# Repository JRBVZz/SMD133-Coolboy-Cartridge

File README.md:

#### COOLBOY - картридж многоигровка для Денди/Famicom

Картридж основан на ASIC **AA6023** в корпусе LQFP-48 с маркировкой **SMD133** и имеет следующие характеристики:
* **PRG ROM**: до 32 МБ
* **CHR RAM**: до 256 КБ
* **PRG RAM**: 8/32 КБ, FRAM или SRAM

Проект создан в [**KiCad 9**](https://www.kicad.org/).

#### Параметры для изготовления PCB
* 2 слоя
* Толщина PCB: 1.2 мм
* Рекомендуется ENIG покрытие контактов краевого разъема

#### Схема
[Schematic PDF](Pics/Coolboy-schematic.pdf)

#### Интерактивный BOM
[BoM](BOM/Coolboy-iBOM.html) (для корректного просмотра нужно скачать raw файл)

#### Прошивка
Для прошивки картриджа без пайки, перемычка должна соединять среднюю и нижнюю площадки у джампера "R/W". Картридж можно перепрошить с помощью [Famicom/NES Dumper/Writer](https://github.com/ClusterM/famicom-dumper-writer), собрать ROM-файл можно в [COOLBOY Multirom Builder](https://github.com/ClusterM/coolboy-multirom-builder). Спасибо Алексею Кластеру за эти отличные инструменты.

PS Герберы не выкладываю специально - это мой небольшой вклад в популяризацию KiCad :smile:

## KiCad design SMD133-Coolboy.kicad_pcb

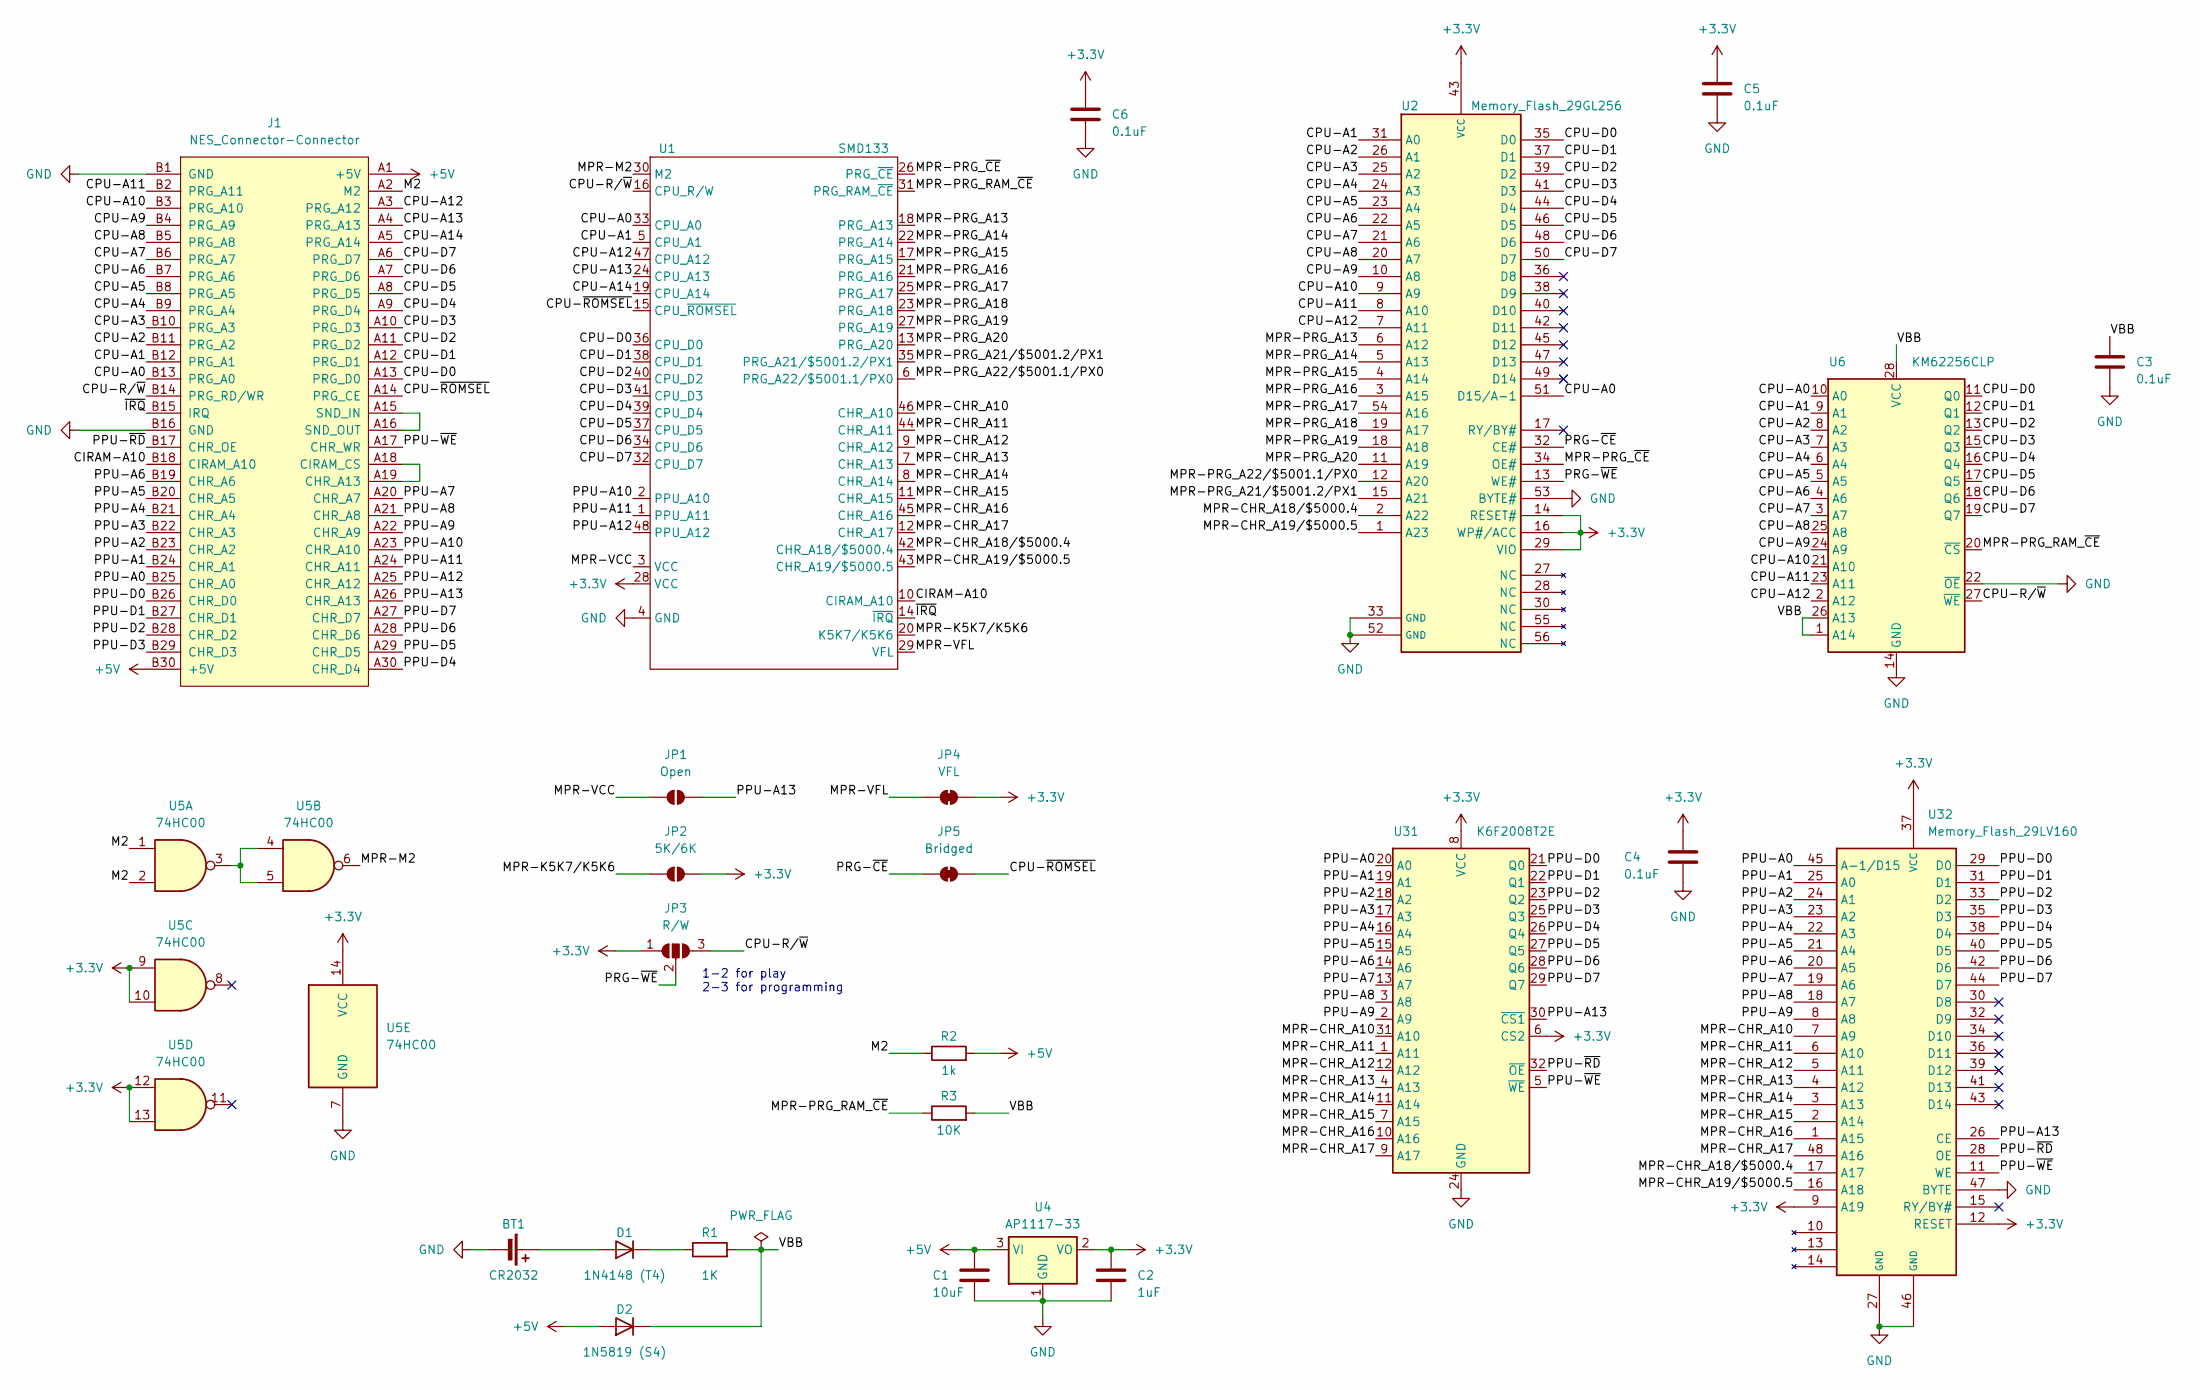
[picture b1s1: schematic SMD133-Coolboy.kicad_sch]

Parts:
BT1: CR2032; BatteryHolder_2032
C1: 10uF; C_0805_2012Metric
C2: 1uF; C_0805_2012Metric
C3, C4, C5, C6: 0.1uF; C_0603_1608Metric_Pad1.08x0.95mm_HandSolder
D1: 1N4148 (T4); D_SOD-123
D2: 1N5819 (S4); D_SOD-123
J1: NES_Connector-Connector; NES_Connector_L
JP1: Open; SolderJumper-2_P1.3mm_Open_RoundedPad1.0x1.5mm
JP2: 5K/6K; SolderJumper-2_P1.3mm_Open_RoundedPad1.0x1.5mm
JP3: R/W; SolderJumper-3_P1.3mm_Open_RoundedPad1.0x1.5mm
JP4: VFL; SolderJumper-2_P1.3mm_Bridged_RoundedPad1.0x1.5mm
JP5: Bridged; SolderJumper-2_P1.3mm_Bridged_RoundedPad1.0x1.5mm
R1: 1K; R_0805_2012Metric
R2: 1k; R_0805_2012Metric
R3: 10K; R_0805_2012Metric
U1: SMD133; LQFP-48_7x7mm_P0.5mm
U2: Memory_Flash_29GL256; TSOP-I-56_18.4x14mm_P0.5mm
U4: AP1117-33; SOT-89-223
U5: 74HC00; SO-14_3.9x8.65mm_P1.27mm
U6: KM62256CLP; SOP-28
U31: K6F2008T2E; TSOP-I-32_11.8-18.4x8mm_P0.5mm
U32: Memory_Flash_29LV160; TSOP-I-48_18.4x12mm_P0.5mm

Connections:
+3.3V: C2.1, C4.1, C5.1, C6.1, JP2.2 (B), JP3.1 (A), JP4.2 (B), U1.28 (VCC), U2.14 (RESET#), U2.16 (WP#/ACC), U2.29 (VIO), U2.43 (VCC), U4.2 (VO), U5.9, U5.10, U5.12, U5.13, U5.14 (VCC), U31.6 (CS2), U31.8 (VCC), U32.9 (A19), U32.12 (RESET), U32.37 (VCC)
+5V: C1.1, D2.2 (A), J1.A1 (+5V), J1.B30 (+5V), R2.2, U4.3 (VI)
/CIRAM-A10: J1.B18 (CIRAM_A10), U1.10 (CIRAM_A10)
/CPU-A0: J1.B13 (PRG_A0), U1.33 (CPU_A0), U2.51 (D15/A-1), U6.10 (A0)
/CPU-A1: J1.B12 (PRG_A1), U1.5 (CPU_A1), U2.31 (A0), U6.9 (A1)
/CPU-A2: J1.B11 (PRG_A2), U2.26 (A1), U6.8 (A2)
/CPU-A3: J1.B10 (PRG_A3), U2.25 (A2), U6.7 (A3)
/CPU-A4: J1.B9 (PRG_A4), U2.24 (A3), U6.6 (A4)
/CPU-A5: J1.B8 (PRG_A5), U2.23 (A4), U6.5 (A5)
/CPU-A6: J1.B7 (PRG_A6), U2.22 (A5), U6.4 (A6)
/CPU-A7: J1.B6 (PRG_A7), U2.21 (A6), U6.3 (A7)
/CPU-A8: J1.B5 (PRG_A8), U2.20 (A7), U6.25 (A8)
/CPU-A9: J1.B4 (PRG_A9), U2.10 (A8), U6.24 (A9)
/CPU-A10: J1.B3 (PRG_A10), U2.9 (A9), U6.21 (A10)
/CPU-A11: J1.B2 (PRG_A11), U2.8 (A10), U6.23 (A11)
/CPU-A12: J1.A3 (PRG_A12), U1.47 (CPU_A12), U2.7 (A11), U6.2 (A12)
/CPU-A13: J1.A4 (PRG_A13), U1.24 (CPU_A13)
/CPU-A14: J1.A5 (PRG_A14), U1.19 (CPU_A14)
/CPU-D0: J1.A13 (PRG_D0), U1.36 (CPU_D0), U2.35 (D0), U6.11 (Q0)
/CPU-D1: J1.A12 (PRG_D1), U1.38 (CPU_D1), U2.37 (D1), U6.12 (Q1)
/CPU-D2: J1.A11 (PRG_D2), U1.40 (CPU_D2), U2.39 (D2), U6.13 (Q2)
/CPU-D3: J1.A10 (PRG_D3), U1.41 (CPU_D3), U2.41 (D3), U6.15 (Q3)
/CPU-D4: J1.A9 (PRG_D4), U1.39 (CPU_D4), U2.44 (D4), U6.16 (Q4)
/CPU-D5: J1.A8 (PRG_D5), U1.37 (CPU_D5), U2.46 (D5), U6.17 (Q5)
/CPU-D6: J1.A7 (PRG_D6), U1.34 (CPU_D6), U2.48 (D6), U6.18 (Q6)
/CPU-D7: J1.A6 (PRG_D7), U1.32 (CPU_D7), U2.50 (D7), U6.19 (Q7)
/CPU-R/~W: J1.B14 (PRG_RD/WR), JP3.3 (B), U1.16 (CPU_R/W), U6.27 (~WE)
/CPU-~ROMSEL: J1.A14 (PRG_CE), JP5.2 (B), U1.15 (CPU_~ROMSEL)
/M2: J1.A2 (M2), R2.1, U5.1, U5.2
/MPR-CHR_A10: U1.46 (CHR_A10), U31.31 (A10), U32.7 (A9)
/MPR-CHR_A11: U1.44 (CHR_A11), U31.1 (A11), U32.6 (A10)
/MPR-CHR_A12: U1.9 (CHR_A12), U31.12 (A12), U32.5 (A11)
/MPR-CHR_A13: U1.7 (CHR_A13), U31.4 (A13), U32.4 (A12)
/MPR-CHR_A14: U1.8 (CHR_A14), U31.11 (A14), U32.3 (A13)
/MPR-CHR_A15: U1.11 (CHR_A15), U31.7 (A15), U32.2 (A14)
/MPR-CHR_A16: U1.45 (CHR_A16), U31.10 (A16), U32.1 (A15)
/MPR-CHR_A17: U1.12 (CHR_A17), U31.9 (A17), U32.48 (A16)
/MPR-CHR_A18/$5000.4: U1.42 (CHR_A18/$5000.4), U2.2 (A22), U32.17 (A17)
/MPR-CHR_A19/$5000.5: U1.43 (CHR_A19/$5000.5), U2.1 (A23), U32.16 (A18)
/MPR-K5K7/K5K6: JP2.1 (A), U1.20 (K5K7/K5K6)
/MPR-M2: U1.30 (M2), U5.6
/MPR-PRG_A13: U1.18 (PRG_A13), U2.6 (A12)
/MPR-PRG_A14: U1.22 (PRG_A14), U2.5 (A13)
/MPR-PRG_A15: U1.17 (PRG_A15), U2.4 (A14)
/MPR-PRG_A16: U1.21 (PRG_A16), U2.3 (A15)
/MPR-PRG_A17: U1.25 (PRG_A17), U2.54 (A16)
/MPR-PRG_A18: U1.23 (PRG_A18), U2.19 (A17)
/MPR-PRG_A19: U1.27 (PRG_A19), U2.18 (A18)
/MPR-PRG_A20: U1.13 (PRG_A20), U2.11 (A19)
/MPR-PRG_A21/$5001.2/PX1: U1.35 (PRG_A21/$5001.2/PX1), U2.15 (A21)
/MPR-PRG_A22/$5001.1/PX0: U1.6 (PRG_A22/$5001.1/PX0), U2.12 (A20)
/MPR-PRG_RAM_~CE: R3.1, U1.31 (PRG_RAM_~CE), U6.20 (~CS)
/MPR-PRG_~CE: U1.26 (PRG_~CE), U2.34 (OE#)
/MPR-VCC: JP1.1 (A), U1.3 (VCC)
/MPR-VFL: JP4.1 (A), U1.29 (VFL)
/PPU-A0: J1.B25 (CHR_A0), U31.20 (A0), U32.45 (A-1/D15)
/PPU-A1: J1.B24 (CHR_A1), U31.19 (A1), U32.25 (A0)
/PPU-A2: J1.B23 (CHR_A2), U31.18 (A2), U32.24 (A1)
/PPU-A3: J1.B22 (CHR_A3), U31.17 (A3), U32.23 (A2)
/PPU-A4: J1.B21 (CHR_A4), U31.16 (A4), U32.22 (A3)
/PPU-A5: J1.B20 (CHR_A5), U31.15 (A5), U32.21 (A4)
/PPU-A6: J1.B19 (CHR_A6), U31.14 (A6), U32.20 (A5)
/PPU-A7: J1.A20 (CHR_A7), U31.13 (A7), U32.19 (A6)
/PPU-A8: J1.A21 (CHR_A8), U31.3 (A8), U32.18 (A7)
/PPU-A9: J1.A22 (CHR_A9), U31.2 (A9), U32.8 (A8)
/PPU-A10: J1.A23 (CHR_A10), U1.2 (PPU_A10)
/PPU-A11: J1.A24 (CHR_A11), U1.1 (PPU_A11)
/PPU-A12: J1.A25 (CHR_A12), U1.48 (PPU_A12)
/PPU-A13: J1.A26 (CHR_A13), JP1.2 (B), U31.30 (~CS1), U32.26 (CE)
/PPU-D0: J1.B26 (CHR_D0), U31.21 (Q0), U32.29 (D0)
/PPU-D1: J1.B27 (CHR_D1), U31.22 (Q1), U32.31 (D1)
/PPU-D2: J1.B28 (CHR_D2), U31.23 (Q2), U32.33 (D2)
/PPU-D3: J1.B29 (CHR_D3), U31.25 (Q3), U32.35 (D3)
/PPU-D4: J1.A30 (CHR_D4), U31.26 (Q4), U32.38 (D4)
/PPU-D5: J1.A29 (CHR_D5), U31.27 (Q5), U32.40 (D5)
/PPU-D6: J1.A28 (CHR_D6), U31.28 (Q6), U32.42 (D6)
/PPU-D7: J1.A27 (CHR_D7), U31.29 (Q7), U32.44 (D7)
/PPU-~RD: J1.B17 (CHR_OE), U31.32 (~OE), U32.28 (OE)
/PPU-~WE: J1.A17 (CHR_WR), U31.5 (~WE), U32.11 (WE)
/PRG-~CE: JP5.1 (A), U2.32 (CE#)
/PRG-~WE: JP3.2 (C), U2.13 (WE#)
/VBB: C3.1, D2.1 (K), R1.2, R3.2, U6.1 (A14), U6.26 (A13), U6.28 (VCC)
/~IRQ: J1.B15 (IRQ), U1.14 (~IRQ)
GND: BT1.2 (-), C1.2, C2.2, C3.2, C4.2, C5.2, C6.2, J1.B1 (GND), J1.B16 (GND), U1.4 (GND), U2.33 (GND), U2.52 (GND), U2.53 (BYTE#), U4.1 (GND), U5.7 (GND), U6.14 (GND), U6.22 (~OE), U31.24 (GND), U32.27 (GND), U32.46 (GND), U32.47 (BYTE)
unnamed: BT1.1 (+), D1.2 (A)
unnamed: D1.1 (K), R1.1
unnamed: J1.A18 (CIRAM_CS), J1.A19 (CHR_A13)
unnamed: J1.A15 (SND_IN), J1.A16 (SND_OUT)
unnamed: U5.3, U5.4, U5.5

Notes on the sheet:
1-2 for play 2-3 for programming

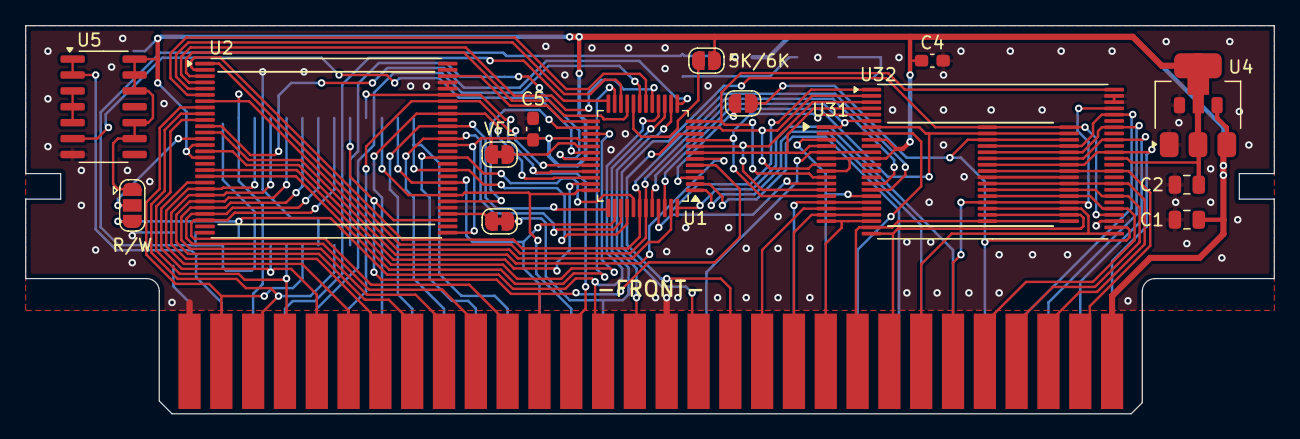
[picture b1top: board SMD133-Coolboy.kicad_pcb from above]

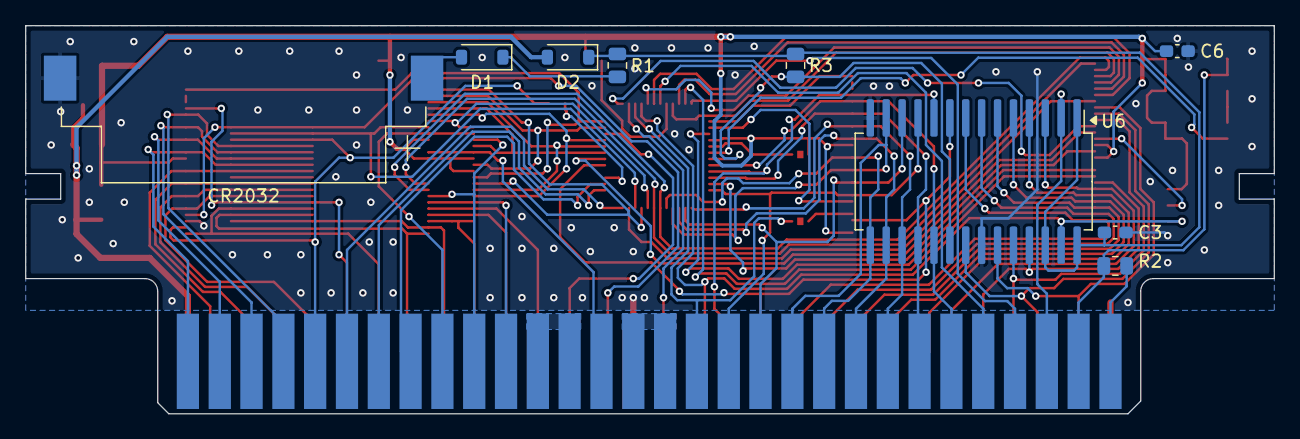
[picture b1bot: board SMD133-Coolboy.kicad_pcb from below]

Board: 2 copper layers, 99.7 x 31.0 mm, 25 parts (9 on the bottom side), 89 nets.

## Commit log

2025-07-10 1st Commit
2025-07-11 Add Schematic
2025-07-11 Add BOM
